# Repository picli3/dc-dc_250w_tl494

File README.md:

# Fuente de poder conmutada
Es una fuente DC-DC que esta disenada para el uso en vehiculos con baterias de 12V, en teoria es capaz de entregar hasta 250W si se usa en transformador adecuado.

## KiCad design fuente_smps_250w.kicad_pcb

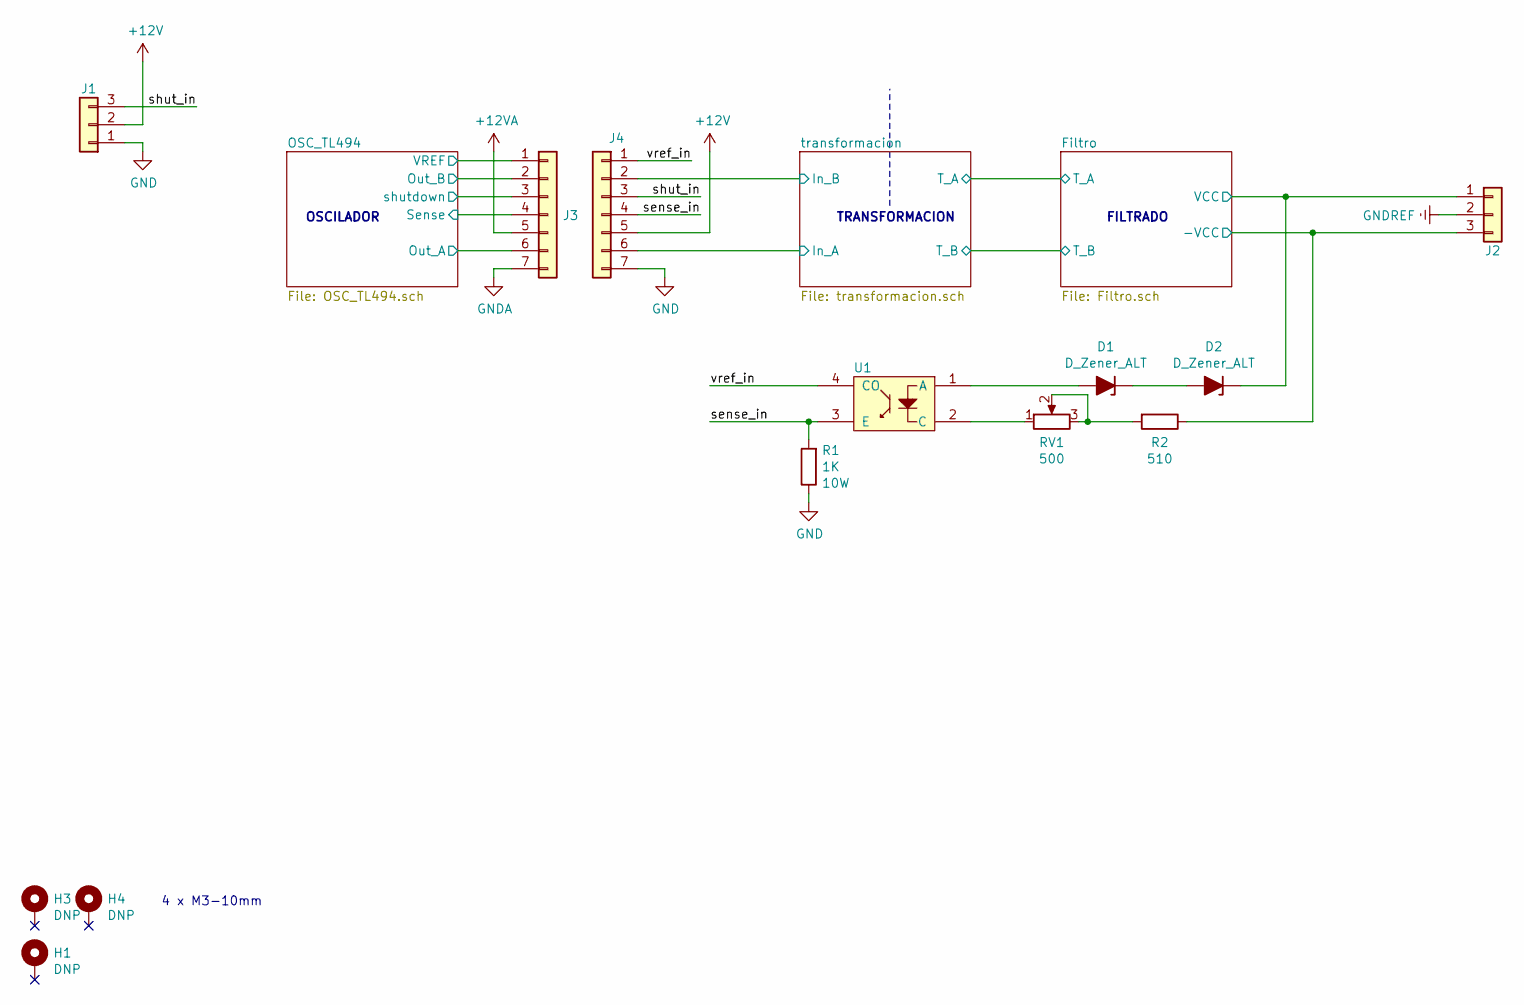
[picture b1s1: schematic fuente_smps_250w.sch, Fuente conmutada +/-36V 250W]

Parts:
D1, D2: D_Zener_ALT; D_A-405_P10.16mm_Horizontal
H1, H3, H4: MountingHole_Pad; MountingHole_3.2mm_M3_Pad_Via; Mfg Part # DNP
J1, J2: Conn_01x03; TerminalBlock_Dinkle_DT-55-B01X-03_P10.00mm
J3: Conn_01x03; PinHeader_1x07_P2.54mm_Horizontal
J4: Conn_01x03; PinSocket_1x07_P2.54mm_Vertical
R1: 1K; R_Axial_DIN0207_L6.3mm_D2.5mm_P10.16mm_Horizontal
R2: 510; R_Axial_DIN0207_L6.3mm_D2.5mm_P10.16mm_Horizontal
RV1: 500; Potentiometer_Runtron_RM-065_Vertical
U1: LTV-817S-TA1; DIP-4_W7.62mm_LongPads

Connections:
+12V: J1.2, J4.5; also elsewhere on the board
/Filtro/-VCC: J2.3, R2.1; also elsewhere on the board
/Filtro/VCC: D2.1 (K), J2.1; also elsewhere on the board
/OSC_TL494/Out_A: J3.6; also elsewhere on the board
/OSC_TL494/Out_B: J3.2; also elsewhere on the board
/OSC_TL494/Sense: J3.4; also elsewhere on the board
/OSC_TL494/VREF: J3.1; also elsewhere on the board
/sense_in: J4.4, R1.2, U1.3 (E)
/shut_in: J1.3, J4.3
/transformacion/In_A: J4.6; also elsewhere on the board
/transformacion/In_B: J4.2; also elsewhere on the board
/vref_in: J4.1, U1.4 (CO)
GND: J1.1, J4.7, R1.1; also elsewhere on the board
GNDA: J3.7; also elsewhere on the board
GNDREF: J2.2; also elsewhere on the board
unnamed: D1.1 (K), D2.2 (A)
unnamed: D1.2 (A), U1.1 (A)
unnamed: R2.2, RV1.2, RV1.3
unnamed: RV1.1, U1.2 (C)

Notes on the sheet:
OSCILADOR
TRANSFORMACION
FILTRADO
4 x M3-10mm

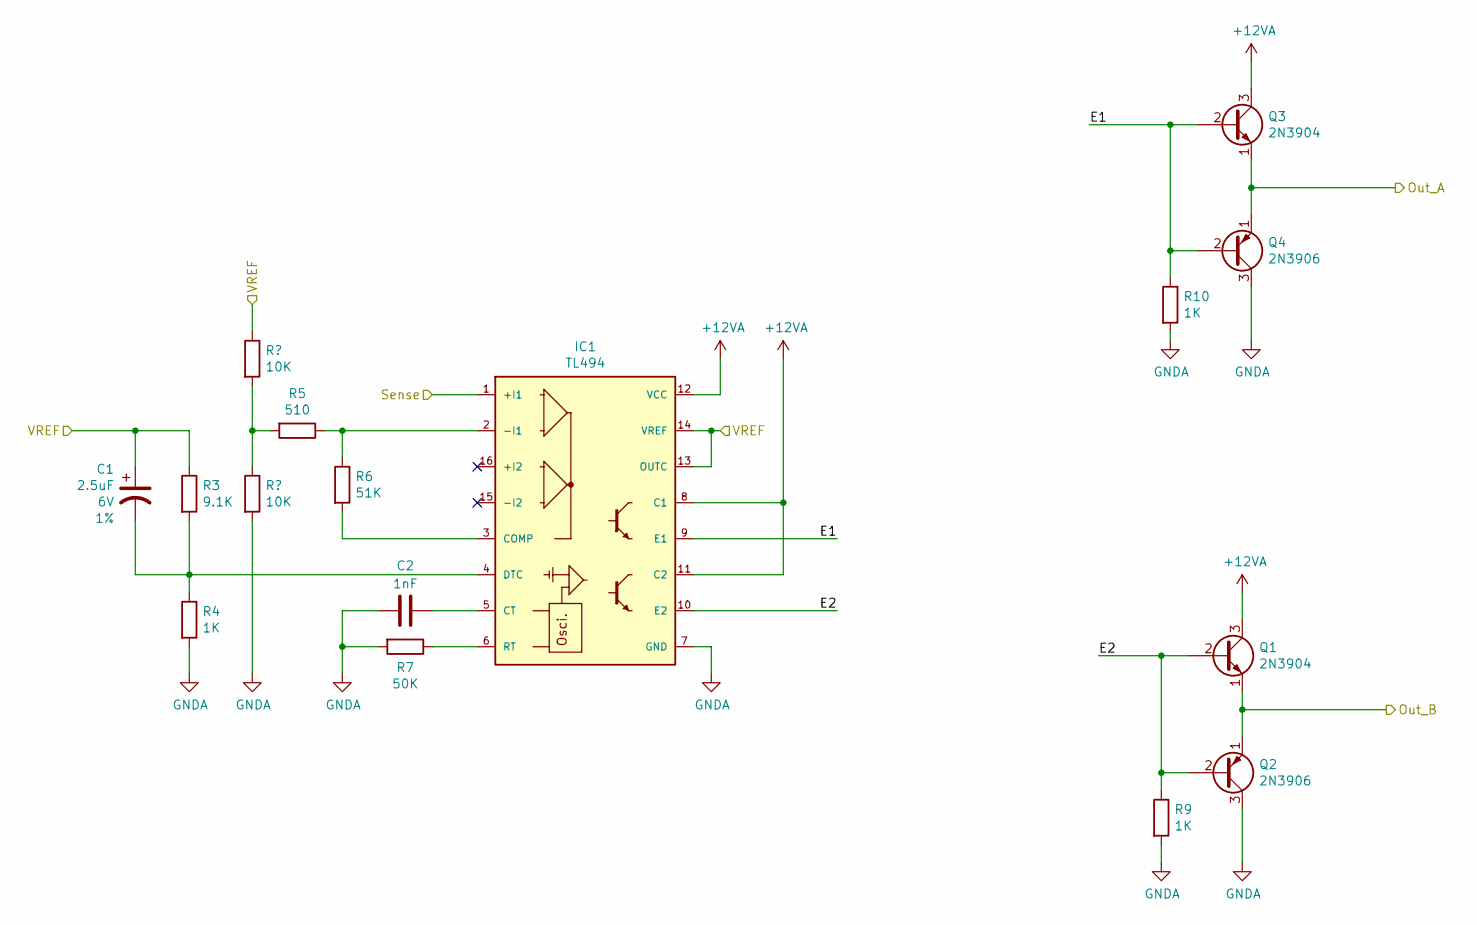
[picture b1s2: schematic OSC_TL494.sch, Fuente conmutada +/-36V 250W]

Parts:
C1: 2.5uF; CP_Radial_D4.0mm_P2.00mm
C2: 1nF; C_Disc_D4.3mm_W1.9mm_P5.00mm
IC1: TL494; DIP-16_W7.62mm_LongPads
Q1, Q3: 2N3904; TO-92L_HandSolder
Q2, Q4: 2N3906; TO-92L_HandSolder
R3: 9.1K; R_Axial_DIN0207_L6.3mm_D2.5mm_P10.16mm_Horizontal
R4, R9, R10: 1K; R_Axial_DIN0207_L6.3mm_D2.5mm_P10.16mm_Horizontal
R5: 510; R_Axial_DIN0207_L6.3mm_D2.5mm_P10.16mm_Horizontal
R6: 51K; R_Axial_DIN0207_L6.3mm_D2.5mm_P10.16mm_Horizontal
R7: 50K; R_Axial_DIN0207_L6.3mm_D2.5mm_P10.16mm_Horizontal

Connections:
/OSC_TL494/E1: IC1.9 (E1), Q3.2 (B), Q4.2 (B), R10.1
/OSC_TL494/E2: IC1.10 (E2), Q1.2 (B), Q2.2 (B), R9.1
/OSC_TL494/Out_A: Q3.1 (E), Q4.1 (E); also elsewhere on the board
/OSC_TL494/Out_B: Q1.1 (E), Q2.1 (E); also elsewhere on the board
/OSC_TL494/Sense: IC1.1 (+I1); also elsewhere on the board
/OSC_TL494/VREF: C1.1, IC1.13 (OUTC), IC1.14 (VREF), R3.1, R5.2; also elsewhere on the board
GNDA: C2.2, IC1.7 (GND), Q2.3 (C), Q4.3 (C), R4.2, R7.2, R9.2, R10.2; also elsewhere on the board
unnamed: C1.2, IC1.4 (DTC), R3.2, R4.1
unnamed: C2.1, IC1.5 (CT)
unnamed: IC1.2 (-I1), R5.1, R6.1
unnamed: IC1.3 (COMP), R6.2
unnamed: IC1.6 (RT), R7.1

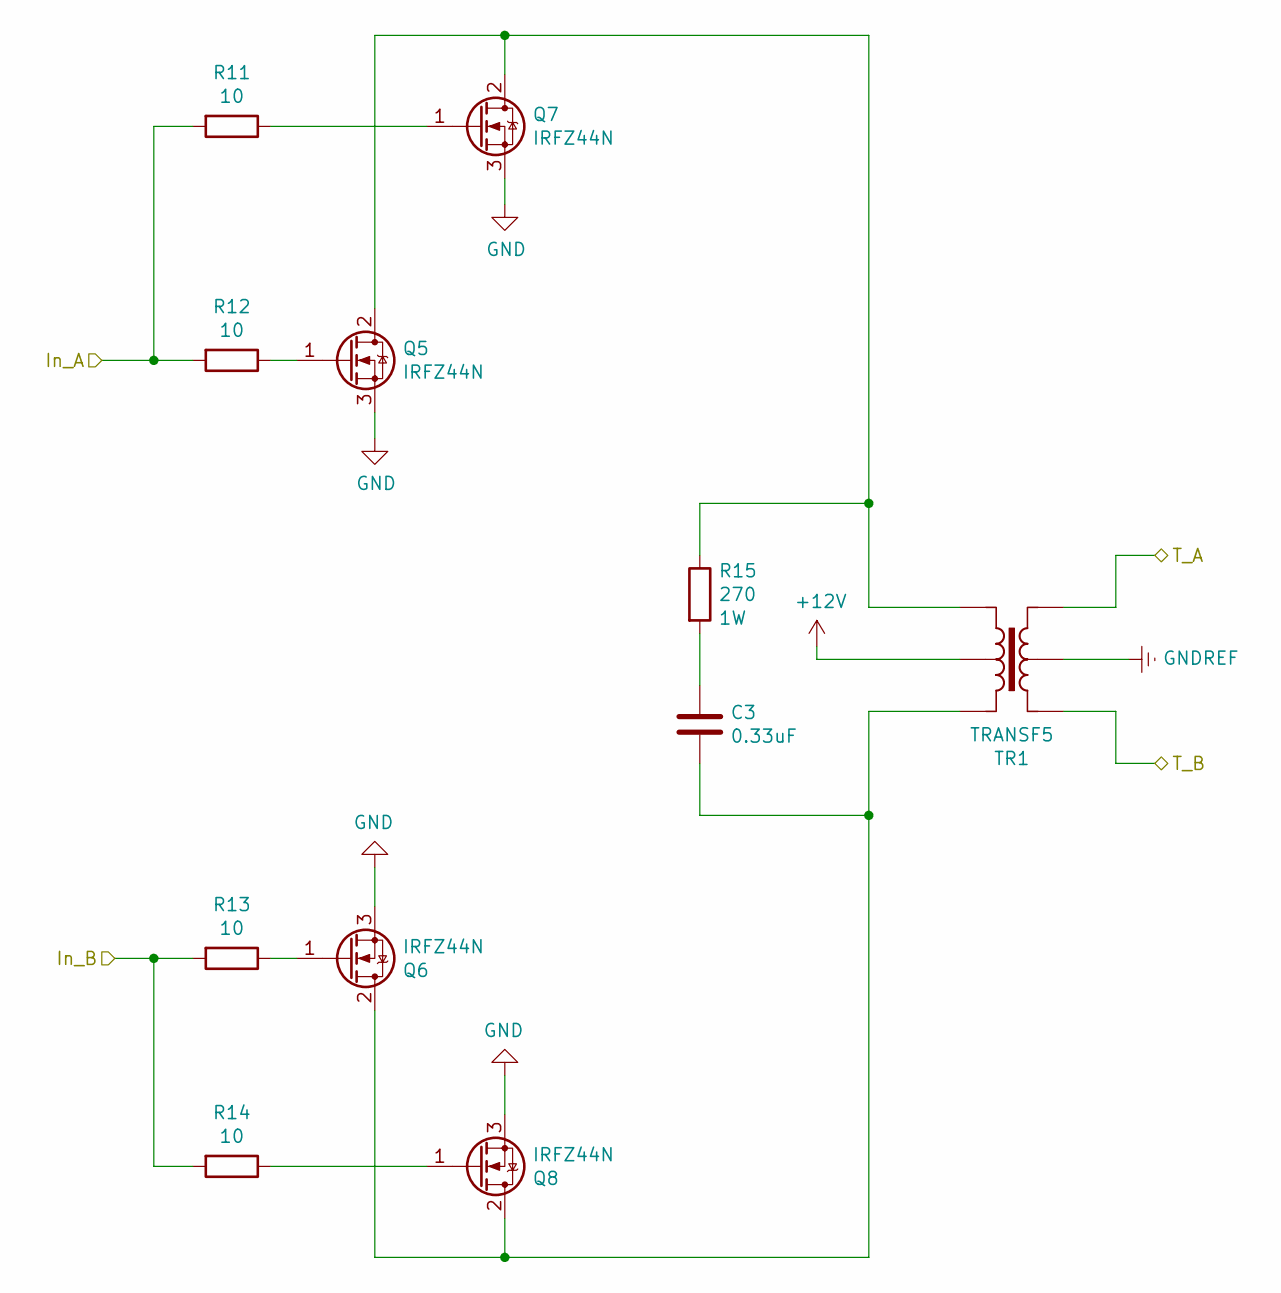
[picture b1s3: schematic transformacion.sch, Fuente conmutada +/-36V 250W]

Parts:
C3: 0.33uF; C_Disc_D4.3mm_W1.9mm_P5.00mm
Q5, Q6, Q7, Q8: IRFZ44N; TO-220-3_Vertical
R11, R12, R13, R14: 10; R_Axial_DIN0207_L6.3mm_D2.5mm_P10.16mm_Horizontal
R15: 270; R_Axial_DIN0309_L9.0mm_D3.2mm_P15.24mm_Horizontal
TR1: TRANSF5; Toroide_40mm

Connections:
+12V: TR1.2; also elsewhere on the board
/Filtro/T_A: TR1.4; also elsewhere on the board
/Filtro/T_B: TR1.6; also elsewhere on the board
/transformacion/In_A: R11.2, R12.2; also elsewhere on the board
/transformacion/In_B: R13.2, R14.2; also elsewhere on the board
GND: Q5.3 (S), Q6.3 (S), Q7.3 (S), Q8.3 (S); also elsewhere on the board
GNDREF: TR1.5; also elsewhere on the board
unnamed: C3.1, R15.2
unnamed: C3.2, Q6.2 (D), Q8.2 (D), TR1.1
unnamed: Q5.1 (G), R12.1
unnamed: Q5.2 (D), Q7.2 (D), R15.1, TR1.3
unnamed: Q6.1 (G), R13.1
unnamed: Q7.1 (G), R11.1
unnamed: Q8.1 (G), R14.1

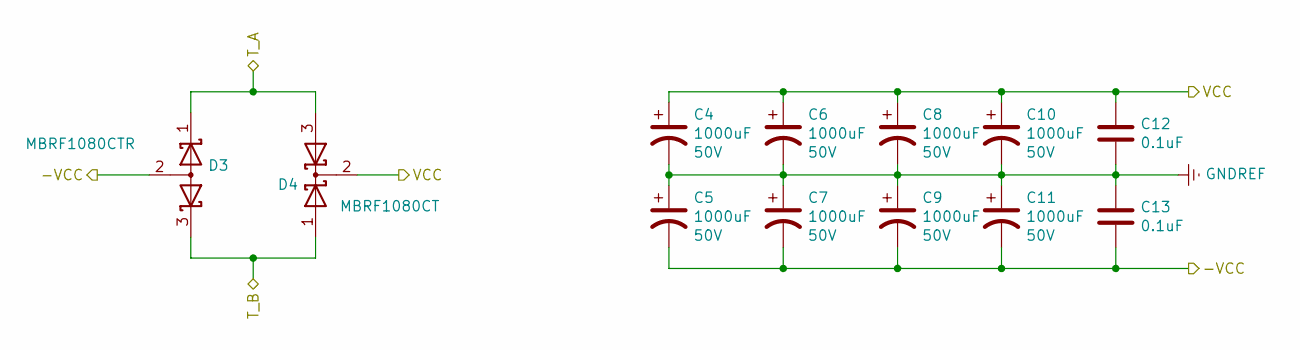
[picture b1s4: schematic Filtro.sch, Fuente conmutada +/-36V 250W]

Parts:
C4, C5, C6, C7, C8, C9, C10, C11: 1000uF; CP_Radial_D10.0mm_P5.00mm
C12, C13: 0.1uF; C_Disc_D3.8mm_W2.6mm_P2.50mm
D3: MBRF1080CTR; TO-220-3_Vertical; Mfg Part # MBRF1080CTR
D4: MBRF1080CT; TO-220-3_Vertical; Mfg Part # MBRF1080CT

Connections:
/Filtro/-VCC: C5.2, C7.2, C9.2, C11.2, C13.2, D3.2 (A); also elsewhere on the board
/Filtro/T_A: D3.1 (K), D4.3 (A); also elsewhere on the board
/Filtro/T_B: D3.3 (K), D4.1 (A); also elsewhere on the board
/Filtro/VCC: C4.1, C6.1, C8.1, C10.1, C12.1, D4.2 (K); also elsewhere on the board
GNDREF: C4.2, C5.1, C6.2, C7.1, C8.2, C9.1, C10.2, C11.1, C12.2, C13.1; also elsewhere on the board

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
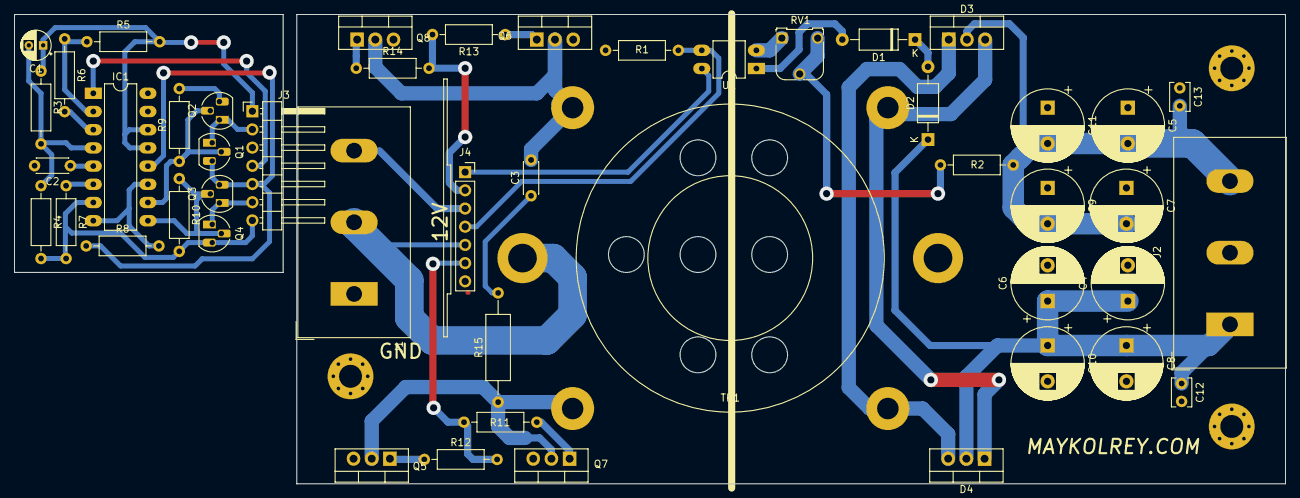
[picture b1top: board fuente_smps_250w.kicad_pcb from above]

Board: 2 copper layers, 177.4 x 65.5 mm, 51 parts (0 on the bottom side), 37 nets.

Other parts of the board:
R8: 10K; R_Axial_DIN0207_L6.3mm_D2.5mm_P10.16mm_Horizontal

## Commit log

2020-10-28 agregando etapa de patencia, aun falta diseño de transformador y diseño de salida
2020-12-17 terminando la version con sg3525a
2020-12-17 agregando readme
2020-12-19 terminando el diseno
2021-11-11 separando el modulo de oscilacion en otra placa
